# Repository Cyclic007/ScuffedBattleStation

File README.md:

# ScuffedBattleStation

This is a custom cooling platorm/dock with a builtin USB-C hub and ethernet adapter. Built for Dell Inspireon 16.

Green is fans and Gold is the PCB spot

# Total cost $119.45

| Part             | cost   | source                                                                                           |
|------------------|--------|--------------------------------------------------------------------------------------------------|
| PCBA + components| $117.39 | JLCPCB                                                                                           |
| fans             | $35.11 | https://www.digikey.com/en/products/detail/same-sky-formerly-cui-devices/CFM-8025V-232-330/7620559       |

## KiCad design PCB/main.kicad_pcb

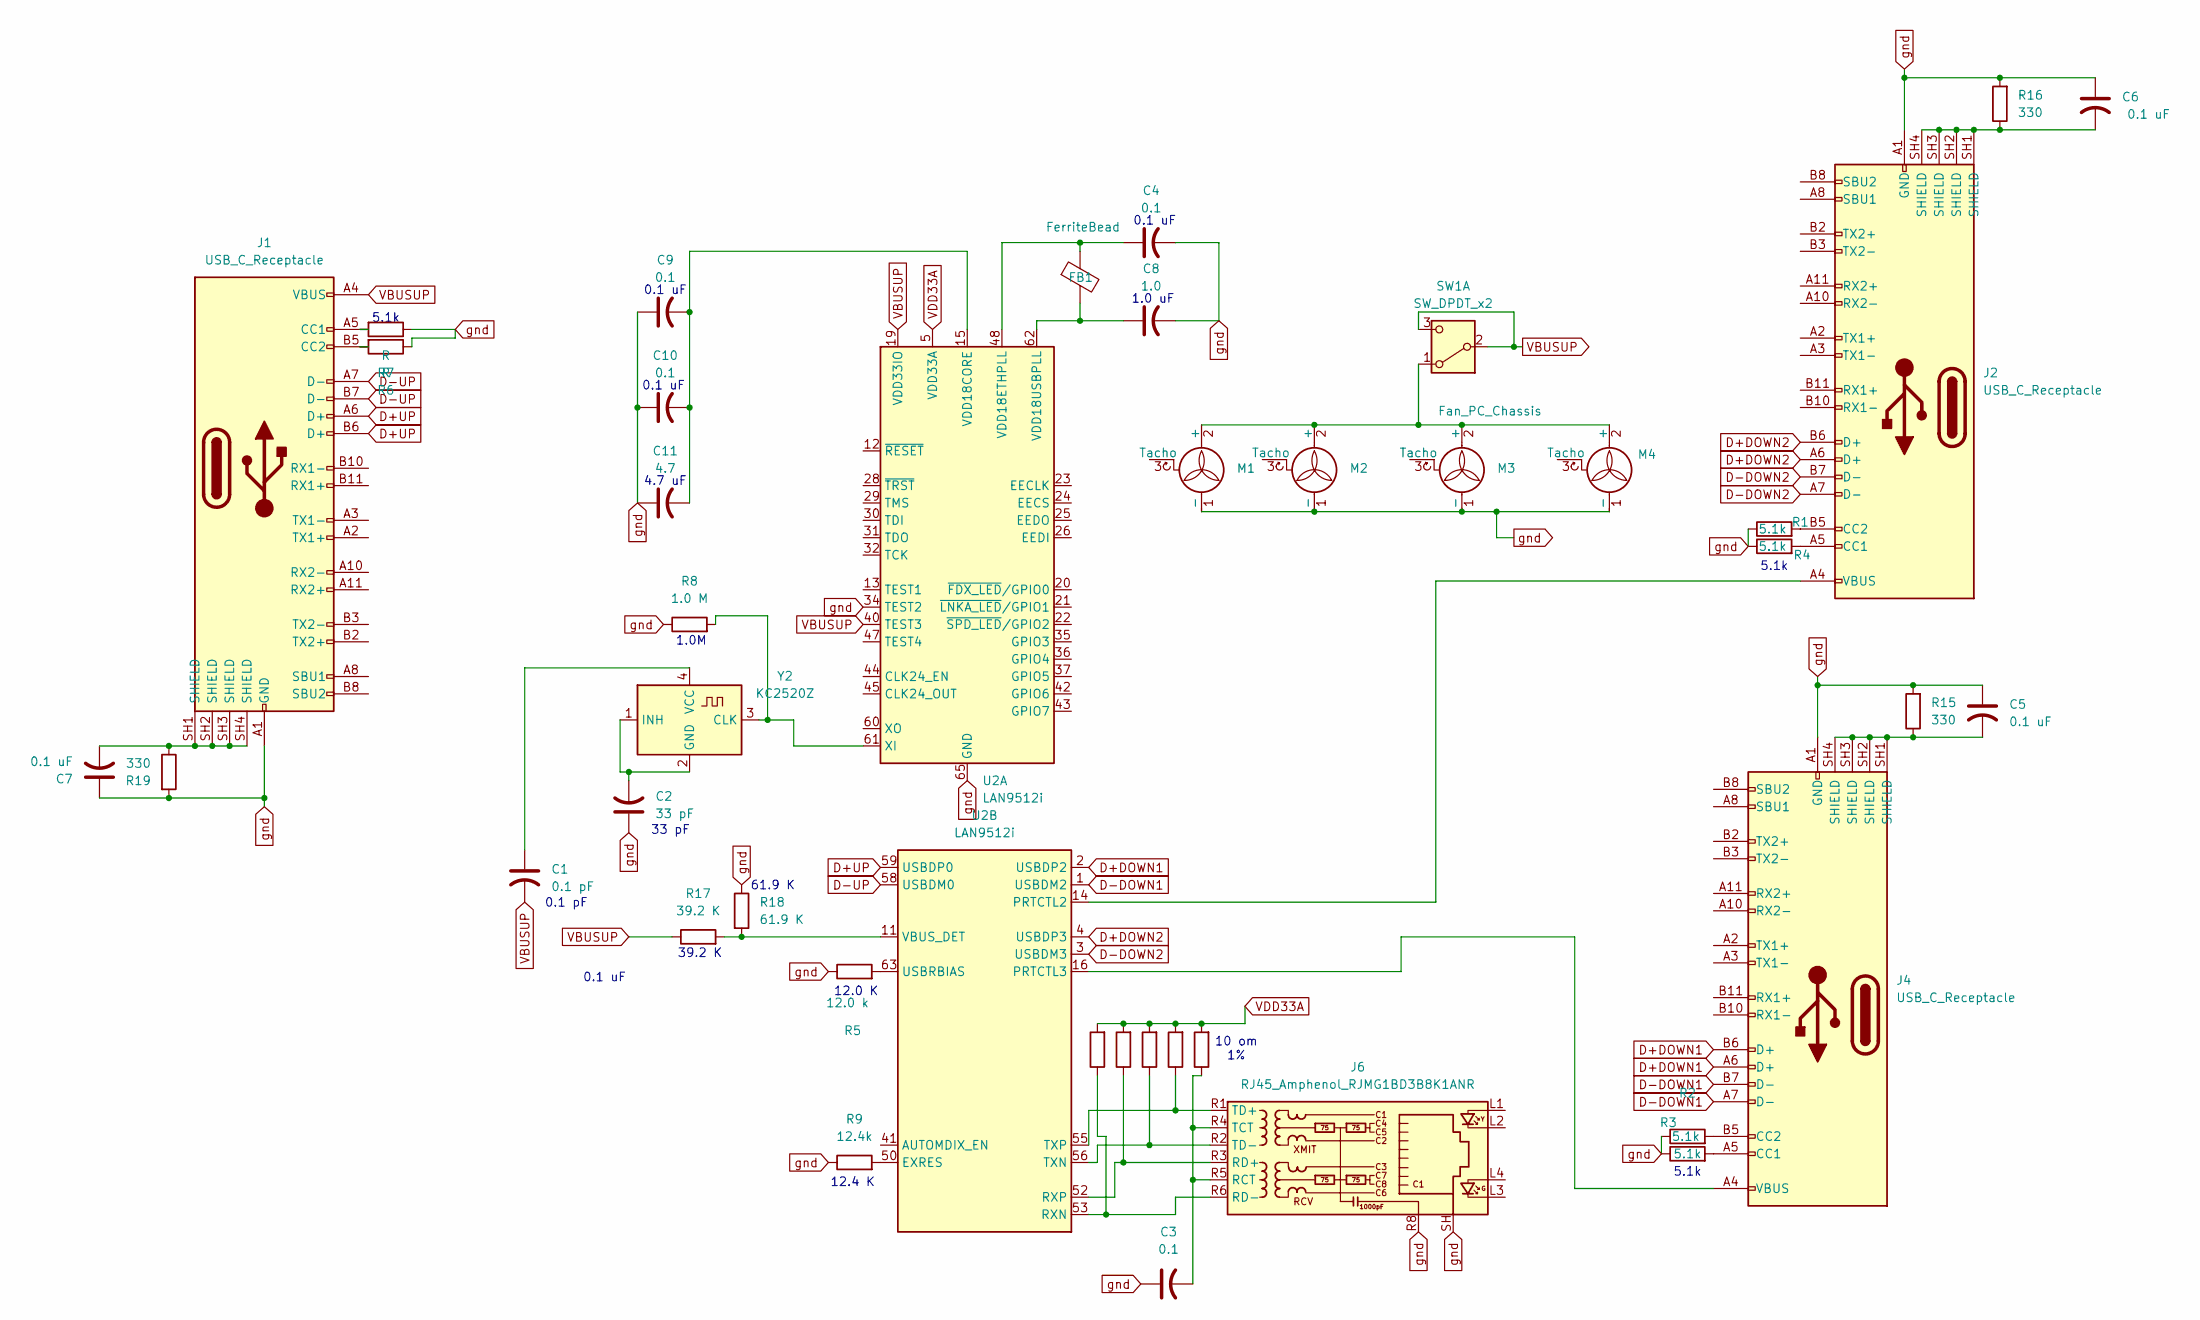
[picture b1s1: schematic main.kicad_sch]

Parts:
C1: 0.1 pF; C_0201_0603Metric
C2: 33 pF; C_0201_0603Metric
C3, C4, C9, C10: 0.1; C_0201_0603Metric
C5, C7: 0.1 uF; C_0201_0603Metric
C6: 330; C_0201_0603Metric
C8: 1.0; C_0201_0603Metric
C11: 4.7; C_0201_0603Metric
FB1: FerriteBead; L_Ferrocore_DLG-0302
J1, J2, J4: USB_C_Receptacle; AMPHENOL_12401826E412A
J6: RJ45_Amphenol_RJMG1BD3B8K1ANR
M1, M2, M3, M4: Fan_PC_Chassis; FanPinHeader_1x03_P2.54mm_Vertical
R1, R2, R3, R4: 5.1k; R_0201_0603Metric
R5: 12.0 k; R_0201_0603Metric
R6, R7: R; R_0201_0603Metric
R8: 1.0 M; R_0201_0603Metric
R9: 12.4k; R_0201_0603Metric
R10, R11, R12, R13, R14: 10; R_0201_0603Metric
R15, R19: 330; R_0201_0603Metric
R16: 0.1 uF; R_0201_0603Metric
R17: 39.2 K; R_0201_0603Metric
R18: 61.9 K; R_0201_0603Metric
SW1: SW_DPDT_x2; SW_CK_JS202011CQN_DPDT_Straight
U2: LAN9512i; QFN-64-1EP_9x9mm_P0.5mm_EP7.3x7.3mm
Y2: KC2520Z; Oscillator_SMD_Kyocera_KC2520Z-4Pin_2.5x2.0mm

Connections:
D+DOWN1: J4.A6 (D+), J4.B6 (D+), U2.2 (USBDP2)
D+DOWN2: J2.A6 (D+), J2.B6 (D+), U2.4 (USBDP3)
D+UP: J1.A6 (D+), J1.B6 (D+), U2.59 (USBDP0)
D-DOWN1: J4.A7 (D-), J4.B7 (D-), U2.1 (USBDM2)
D-DOWN2: J2.A7 (D-), J2.B7 (D-), U2.3 (USBDM3)
D-UP: J1.A7 (D-), J1.B7 (D-), U2.58 (USBDM0)
unnamed: C5.2, J4.SH1 (SHIELD), J4.SH2 (SHIELD), J4.SH3 (SHIELD), J4.SH4 (SHIELD), R15.1
unnamed: C6.2, J2.SH1 (SHIELD), J2.SH2 (SHIELD), J2.SH3 (SHIELD), J2.SH4 (SHIELD), R16.1
unnamed: C7.2, J1.SH1 (SHIELD), J1.SH2 (SHIELD), J1.SH3 (SHIELD), J1.SH4 (SHIELD), R19.1
unnamed: C9.2, C10.2, C11.2, U2.15 (VDD18CORE), U2.38 (VDD18CORE)
unnamed: J1.A5 (CC1), R7.2
unnamed: J1.B5 (CC2), R6.2
unnamed: J2.A5 (CC1), R4.2
unnamed: J2.B5 (CC2), R1.2
unnamed: J4.A5 (CC1), R3.2
unnamed: J4.B5 (CC2), R2.2
unnamed: C3.2, J6.R4 (TCT), J6.R5 (RCT), R14.1
unnamed: J6.R3 (RD+), R11.1, U2.52 (RXP)
unnamed: J6.R6 (RD-), R10.1, U2.53 (RXN)
unnamed: J6.R1 (TD+), R13.1, U2.55 (TXP)
unnamed: J6.R2 (TD-), R12.1, U2.56 (TXN)
unnamed: M1.2 (+), M2.2 (+), M3.2 (+), M4.2 (+), SW1.1 (A)
unnamed: C4.1, FB1.1, U2.48 (VDD18ETHPLL)
unnamed: C8.1, FB1.2, U2.62 (VDD18USBPLL)
unnamed: R8.2, U2.61 (XI), Y2.3 (CLK)
unnamed: R9.2, U2.50 (EXRES)
unnamed: J2.A4 (VBUS), J2.A9 (VBUS), J2.B4 (VBUS), J2.B9 (VBUS), U2.14 (PRTCTL2)
unnamed: J4.A4 (VBUS), J4.A9 (VBUS), J4.B4 (VBUS), J4.B9 (VBUS), U2.16 (PRTCTL3)
unnamed: R5.2, U2.63 (USBRBIAS)
unnamed: R17.2, R18.2, U2.11 (VBUS_DET)
unnamed: C2.2, Y2.1 (INH), Y2.2 (GND)
unnamed: C1.1, Y2.4 (VCC)
VBUSUP: C1.2, J1.A4 (VBUS), J1.A9 (VBUS), J1.B4 (VBUS), J1.B9 (VBUS), R17.1, SW1.2 (B), SW1.3 (C), U2.19 (VDD33IO), U2.27 (VDD33IO), U2.33 (VDD33IO), U2.39 (VDD33IO), U2.40 (TEST3), U2.46 (VDD33IO)
VDD33A: R10.2, R11.2, R12.2, R13.2, R14.2, U2.5 (VDD33A), U2.10 (VDD33A), U2.49 (VDD33A), U2.51 (VDD33A), U2.54 (VDD33A), U2.57 (VDD33A), U2.64 (VDD33A)
gnd: C2.1, C3.1, C4.2, C5.1, C6.1, C7.1, C8.2, C9.1, C10.1, C11.1, J1.A1 (GND), J1.A12 (GND), J1.B1 (GND), J1.B12 (GND), J2.A1 (GND), J2.A12 (GND), J2.B1 (GND), J2.B12 (GND), J4.A1 (GND), J4.A12 (GND), J4.B1 (GND), J4.B12 (GND), J6.R8, J6.SH, M1.1 (-), M2.1 (-), M3.1 (-), M4.1 (-), R1.1, R2.1, R3.1, R4.1, R5.1, R6.1, R7.1, R8.1, R9.1, R15.2, R16.2, R18.1, R19.2, U2.34 (TEST2), U2.65 (GND)

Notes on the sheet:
0.1 uF
61.9 K
33 pF
5.1k
0.1 pF
10 om 1%
12.4 K
39.2 K
4.7 uF
12.0 K
1.0 uF
1.0M

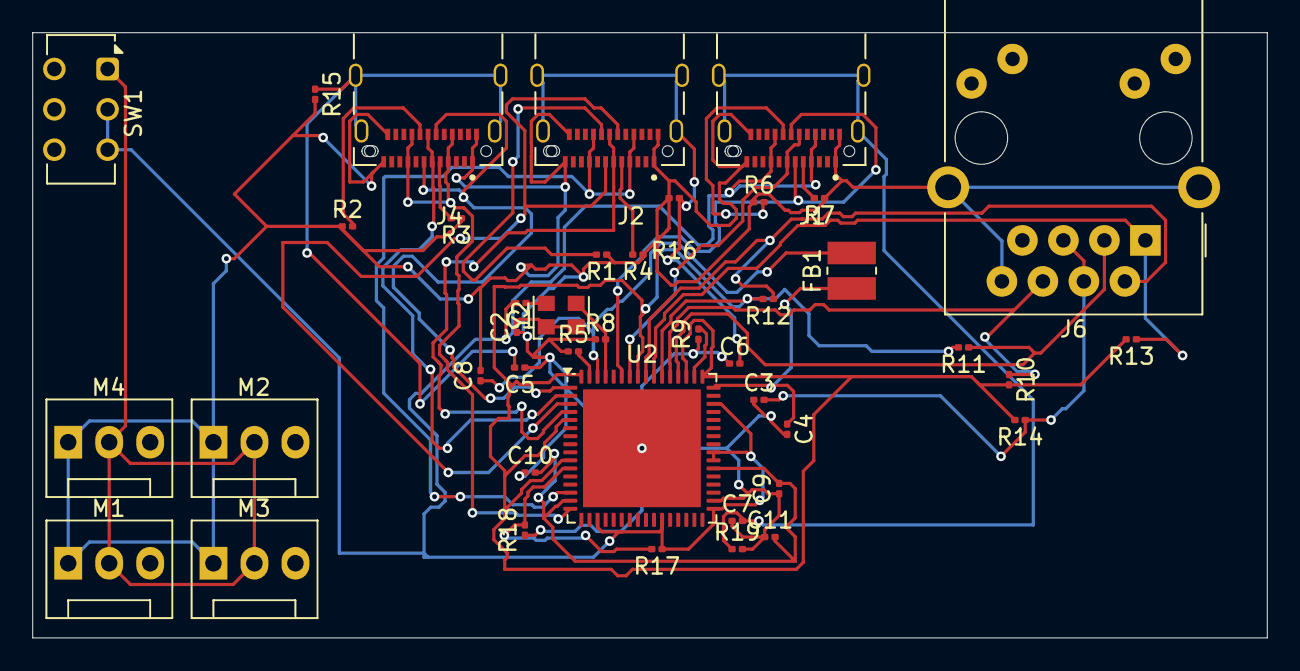
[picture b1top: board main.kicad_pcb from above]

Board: 2 copper layers, 76.5 x 37.5 mm, 42 parts (0 on the bottom side), 35 nets.

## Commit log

2025-06-05 start
2025-06-07 doin stuff
2025-06-11 making cool stuff
2025-06-12 getting stuff done
2025-06-12 adding stuff
2025-06-12 adding BOM
2025-06-14 fixing PCB
2025-06-20 fixing things
2025-06-21 fixing lots of things
2025-06-22 fixing caps
2025-06-23 added full assembley
2025-07-08 fixing footprints
2025-07-11 happy times
